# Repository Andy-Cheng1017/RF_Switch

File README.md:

# RF_Switch
EMPass Automatic control RF Switch device

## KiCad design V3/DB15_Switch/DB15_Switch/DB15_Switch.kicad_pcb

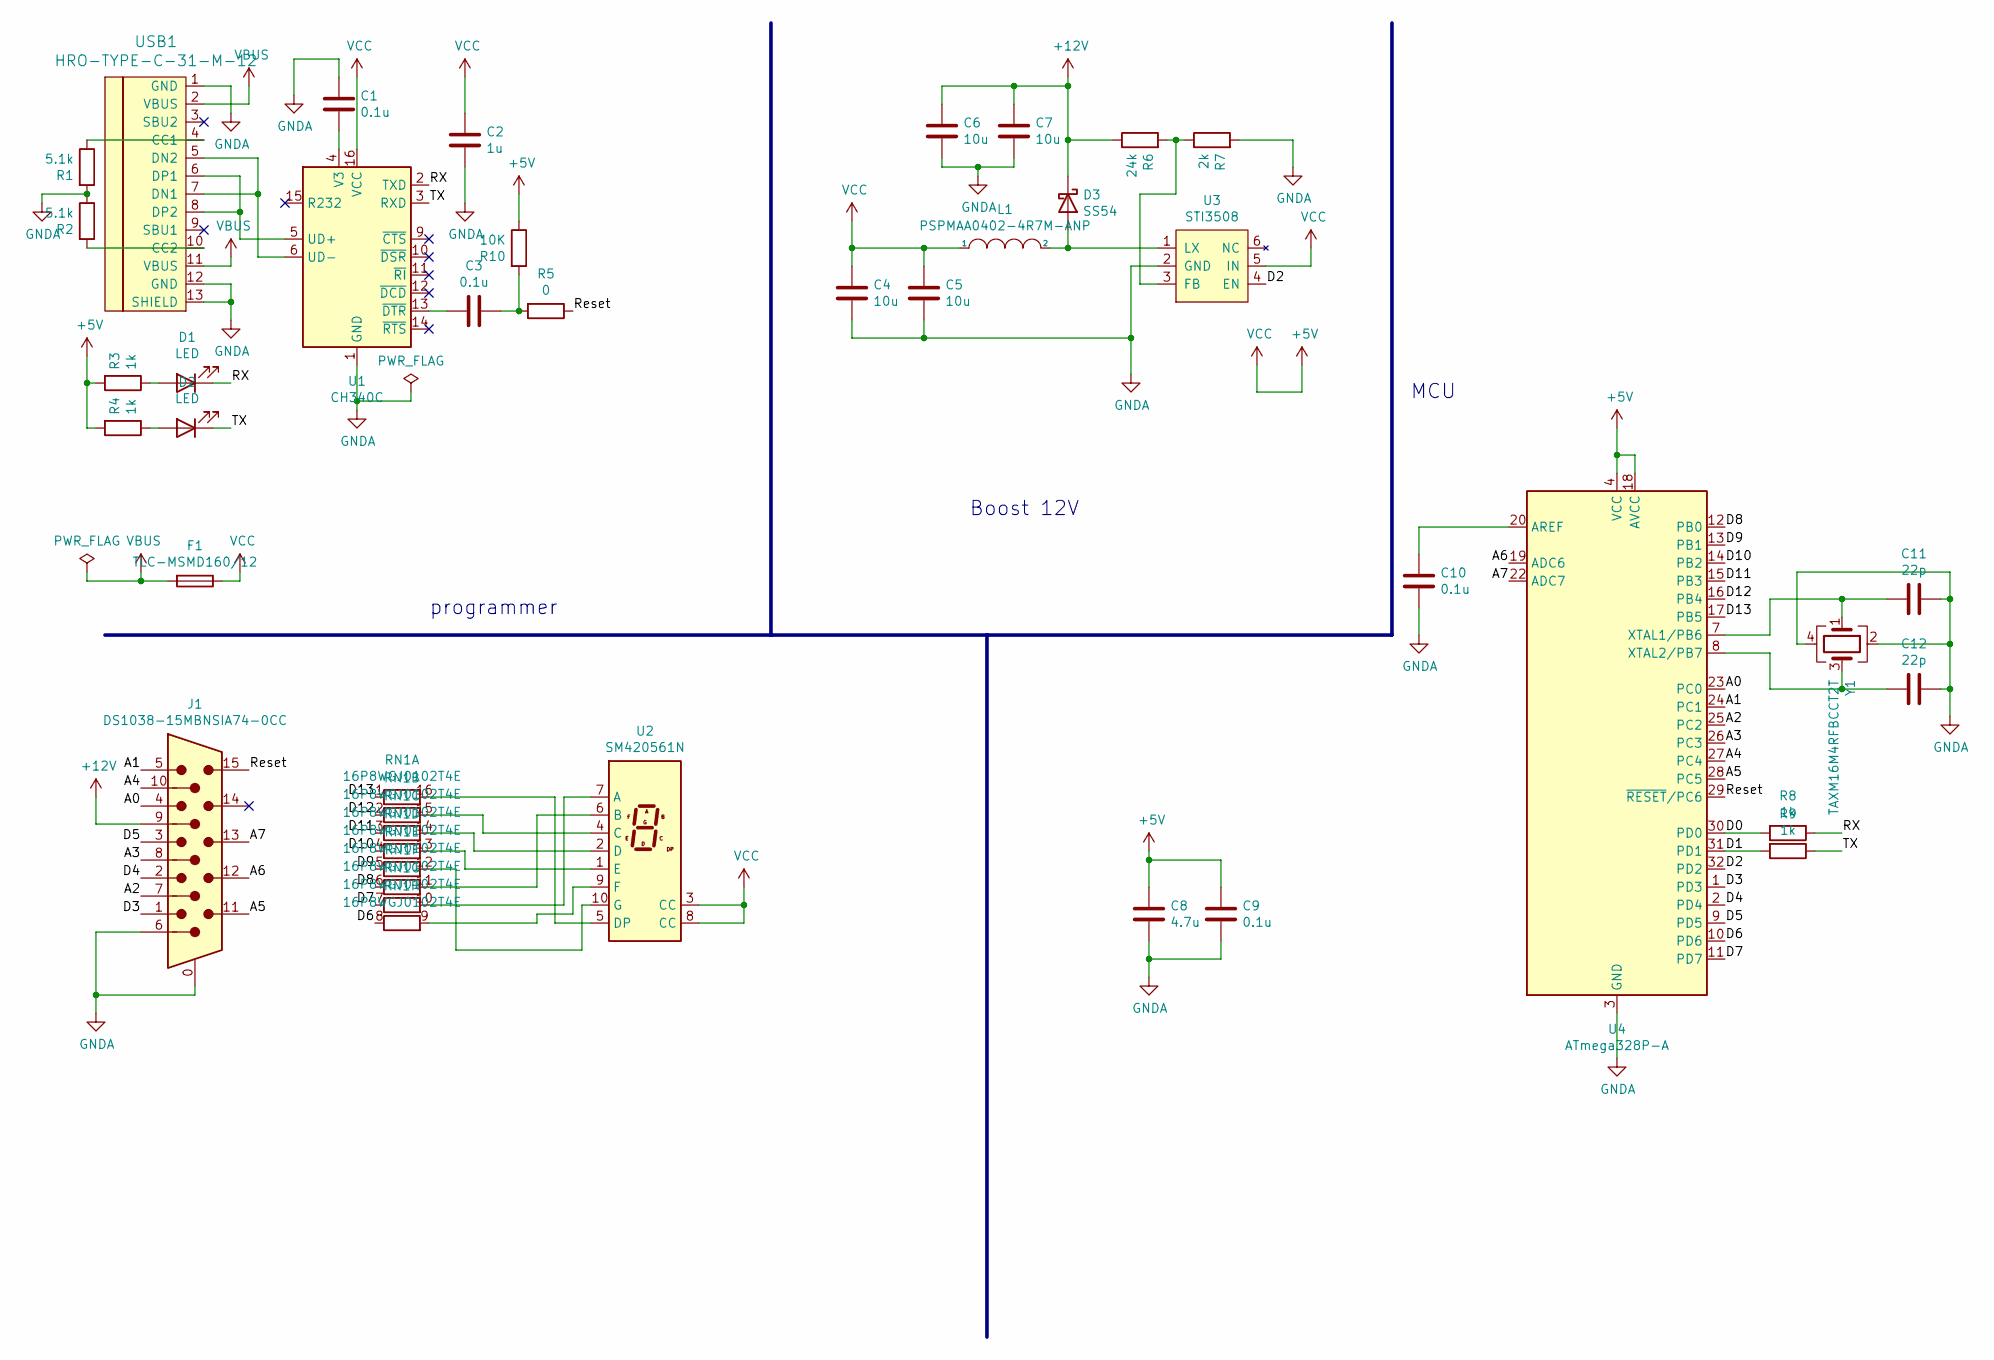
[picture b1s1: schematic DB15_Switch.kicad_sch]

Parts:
C1, C3, C9, C10: 0.1u; C_0805_2012Metric
C2: 1u; C_0805_2012Metric
C4, C5, C6, C7: 10u; C_1206_3216Metric
C8: 4.7u; C_0805_2012Metric
C11, C12: 22p; C_0805_2012Metric
D1, D2: LED; LED_0805_2012Metric
D3: SS54; D_SMA
F1: TLC-MSMD160/12; Fuse_1812_4532Metric
J1: DS1038-15MBNSIA74-0CC; CONN-TH_DS1038-15MBNSIA74-0CC
L1: PSPMAA0402-4R7M-ANP; IND-SMD_L4.5-W4.2
R1, R2: 5.1k; R_0805_2012Metric
R3, R4, R8, R9: 1k; R_0805_2012Metric
R5: 0; R_0402_1005Metric
R6: 24k; R_0805_2012Metric
R7: 2k; R_0805_2012Metric
R10: 10K; R_0805_2012Metric
RN1: 16P8WGJ0102T4E; R_Array_Convex_8x0602
U1: CH340C; SOIC-16_3.9x9.9mm_P1.27mm
U2: SM420561N; 7SegmentLED_LTS6760_LTS6780
U3: STI3508; SOT-23-6
U4: ATmega328P-A; TQFP-32_7x7mm_P0.8mm
USB1: HRO-TYPE-C-31-M-12
Y1: TAXM16M4RFBCCT2T; Crystal_SMD_3225-4Pin_3.2x2.5mm

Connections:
+5V: C2.2, C4.2, C5.2, C8.2, C9.2, F1.1, L1.1, R3.2, R4.2, R10.1, U1.16 (VCC), U2.3 (CC), U2.8 (CC), U3.5 (IN), U4.4 (VCC), U4.6 (VCC), U4.18 (AVCC)
+12V: C6.2, C7.2, D3.1 (K), J1.9, R6.1
/A0: J1.4, U4.23 (PC0)
/A1: J1.5, U4.24 (PC1)
/A2: J1.7, U4.25 (PC2)
/A3: J1.8, U4.26 (PC3)
/A4: J1.10, U4.27 (PC4)
/A5: J1.11, U4.28 (PC5)
/A6: J1.12, U4.19 (ADC6)
/A7: J1.13, U4.22 (ADC7)
/D0: R8.2, U4.30 (PD0)
/D1: R9.2, U4.31 (PD1)
/D2: U3.4 (EN), U4.32 (PD2)
/D3: J1.1, U4.1 (PD3)
/D4: J1.2, U4.2 (PD4)
/D5: J1.3, U4.9 (PD5)
/D6: RN1.8 (R8.1), U4.10 (PD6)
/D7: RN1.7 (R7.1), U4.11 (PD7)
/D8: RN1.6 (R6.1), U4.12 (PB0)
/D9: RN1.5 (R5.1), U4.13 (PB1)
/D10: RN1.4 (R4.1), U4.14 (PB2)
/D11: RN1.3 (R3.1), U4.15 (PB3)
/D12: RN1.2 (R2.1), U4.16 (PB4)
/D13: RN1.1 (R1.1), U4.17 (PB5)
/RX: D1.1 (K), R8.1, U1.2 (TXD)
/Reset: J1.15, R5.1, U4.29 (~RESET/PC6)
/TX: D2.1 (K), R9.1, U1.3 (RXD)
GNDA: C1.2, C2.1, C4.1, C5.1, C6.1, C7.1, C8.1, C9.1, C10.1, C11.1, C12.1, J1.0, J1.6, R1.2, R2.1, R7.2, U1.1 (GND), U3.2 (GND), U4.3 (GND), U4.5 (GND), U4.21 (GND), USB1.1 (GND), USB1.12 (GND), USB1.13 (SHIELD), Y1.2, Y1.4
unnamed: C1.1, U1.4 (V3)
unnamed: C3.1, R5.2, R10.2
unnamed: C3.2, U1.13 (~DTR)
unnamed: C10.2, U4.20 (AREF)
unnamed: C11.2, U4.7 (XTAL1/PB6), Y1.1
unnamed: C12.2, U4.8 (XTAL2/PB7), Y1.3
unnamed: D1.2 (A), R3.1
unnamed: D2.2 (A), R4.1
unnamed: D3.2 (A), L1.2, U3.1 (LX)
unnamed: R1.1, USB1.4 (CC1)
unnamed: R2.2, USB1.10 (CC2)
unnamed: R6.2, R7.1, U3.3 (FB)
unnamed: RN1.9 (R8.2), U2.9 (F)
unnamed: RN1.10 (R7.2), U2.7 (A)
unnamed: RN1.11 (R6.2), U2.6 (B)
unnamed: RN1.12 (R5.2), U2.10 (G)
unnamed: RN1.13 (R4.2), U2.1 (E)
unnamed: RN1.14 (R3.2), U2.2 (D)
unnamed: RN1.15 (R2.2), U2.4 (C)
unnamed: RN1.16 (R1.2), U2.5 (DP)
unnamed: U1.5 (UD+), USB1.6 (DP1), USB1.8 (DP2)
unnamed: U1.6 (UD-), USB1.5 (DN2), USB1.7 (DN1)
VBUS: F1.2, USB1.2 (VBUS), USB1.11 (VBUS)

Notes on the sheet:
Boost 12V
MCU
programmer

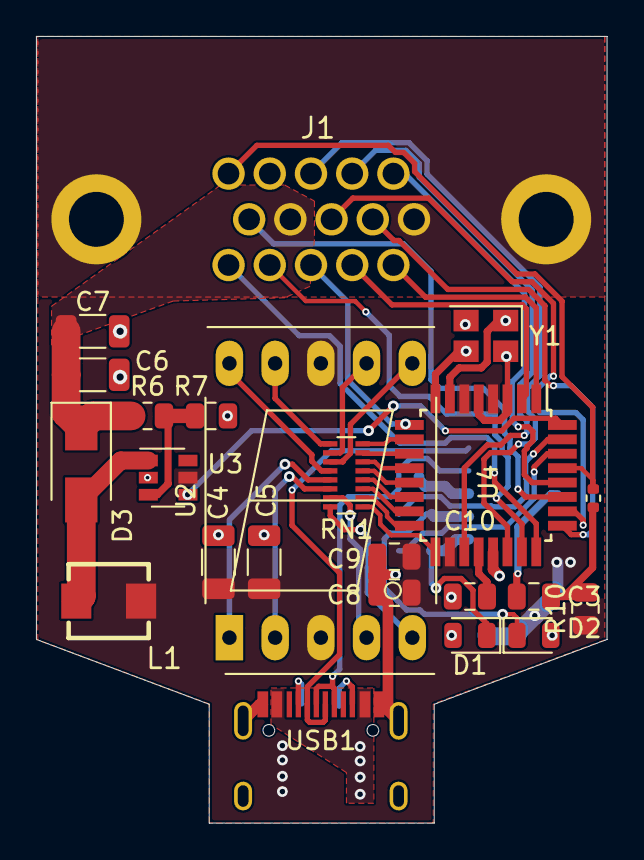
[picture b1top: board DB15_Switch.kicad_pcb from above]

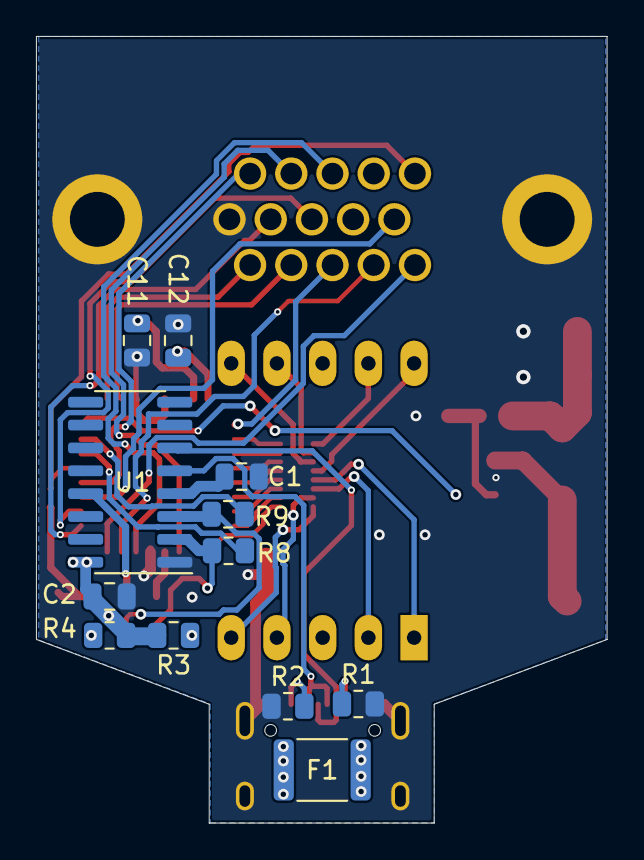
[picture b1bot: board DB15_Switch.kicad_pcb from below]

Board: 2 copper layers, 31.7 x 43.7 mm, 35 parts (12 on the bottom side), 51 nets.

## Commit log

2022-05-25 first upload
2022-05-25 add V2 program
